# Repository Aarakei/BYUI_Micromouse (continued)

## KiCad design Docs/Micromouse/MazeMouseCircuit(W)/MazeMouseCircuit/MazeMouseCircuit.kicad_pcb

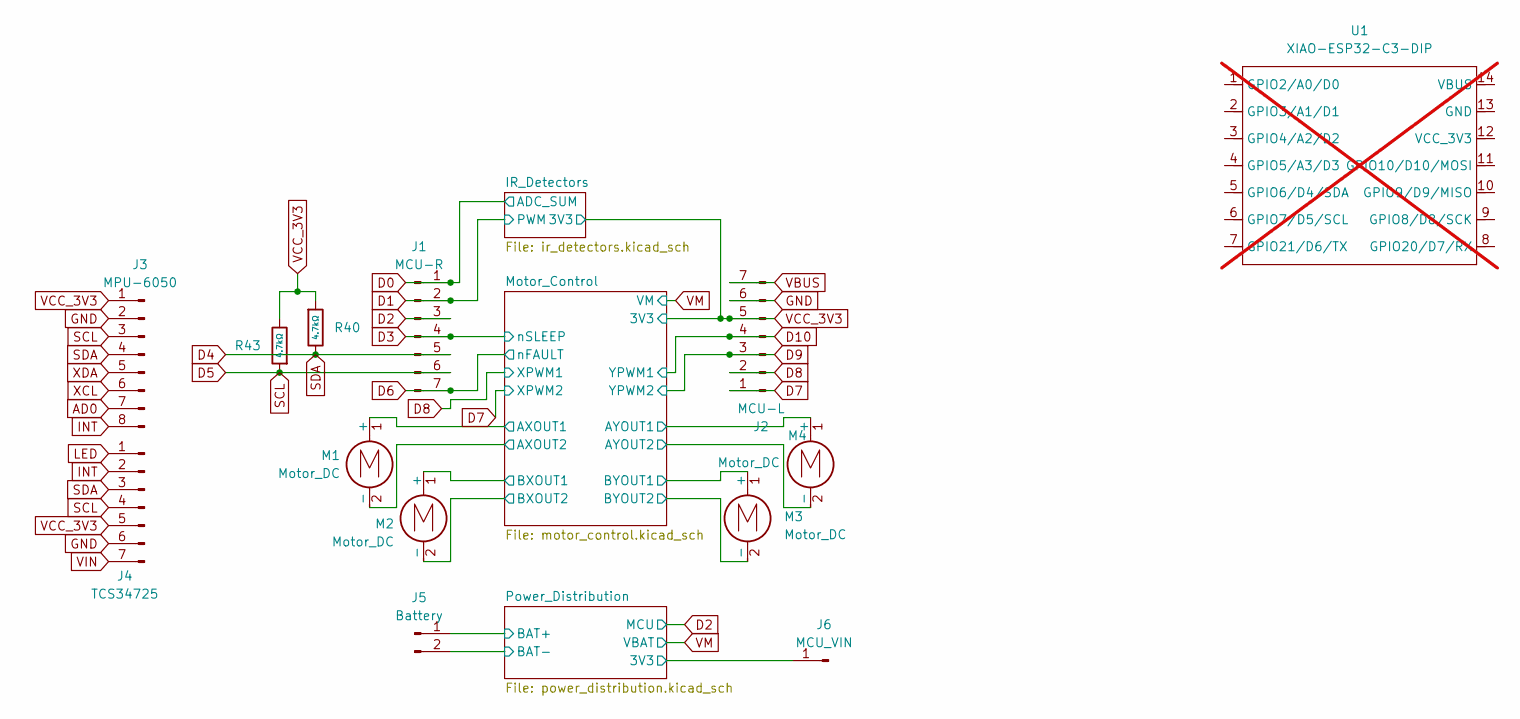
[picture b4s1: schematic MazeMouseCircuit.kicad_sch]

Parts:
J1: MCU-R; PinHeader_1x07_P2.54mm_Vertical
J2: MCU-L; PinHeader_1x07_P2.54mm_Vertical
J3: MPU-6050; PinHeader_1x08_P2.54mm_Vertical
J4: TCS34725; PinHeader_1x07_P2.54mm_Vertical
J5: Battery; PhoenixContact_GMSTBVA_2,5_2-G_1x02_P7.50mm_Vertical
J6: MCU_VIN; PinHeader_1x01_P2.00mm_Vertical
M1, M2, M3, M4: Motor_DC; PinHeader_2x01_P2.54mm_Vertical
R40, R43: 4.7kΩ; R_0402; Overload Voltage (Max) 50V; Tolerance ±1%; Part 0402WGF4701TCE; LCSC C25900
U1: XIAO-ESP32-C3-DIP; MOUDLE14P-XIAO-DIP-SMD; not fitted

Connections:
/Motor_Control/AXOUT1: M1.1 (+); also elsewhere on the board
/Motor_Control/AXOUT2: M1.2 (-); also elsewhere on the board
/Motor_Control/AYOUT1: M4.1 (+); also elsewhere on the board
/Motor_Control/AYOUT2: M4.2 (-); also elsewhere on the board
/Motor_Control/BXOUT1: M2.1 (+); also elsewhere on the board
/Motor_Control/BXOUT2: M2.2 (-); also elsewhere on the board
/Motor_Control/BYOUT1: M3.1 (+); also elsewhere on the board
/Motor_Control/BYOUT2: M3.2 (-); also elsewhere on the board
/Power_Distribution/3V3: J6.1; also elsewhere on the board
/Power_Distribution/BAT+: J5.1; also elsewhere on the board
AD0: J3.7
D0: J1.1; also elsewhere on the board
D1: J1.2; also elsewhere on the board
D2: J1.3; also elsewhere on the board
D3: J1.4; also elsewhere on the board
D4: J1.5, J3.4, J4.3, R40.2
D5: J1.6, J3.3, J4.4, R43.1
D6: J1.7; also elsewhere on the board
D7: J2.1; also elsewhere on the board
D8: J2.2; also elsewhere on the board
D9: J2.3; also elsewhere on the board
D10: J2.4; also elsewhere on the board
GND: J2.6, J3.2, J4.6, J5.2; also elsewhere on the board
INT: J3.8, J4.2
LED: J4.1
VBUS: J2.7
VCC_3V3: J2.5, J3.1, J4.5, R40.1, R43.2; also elsewhere on the board
VIN: J4.7
XCL: J3.6
XDA: J3.5

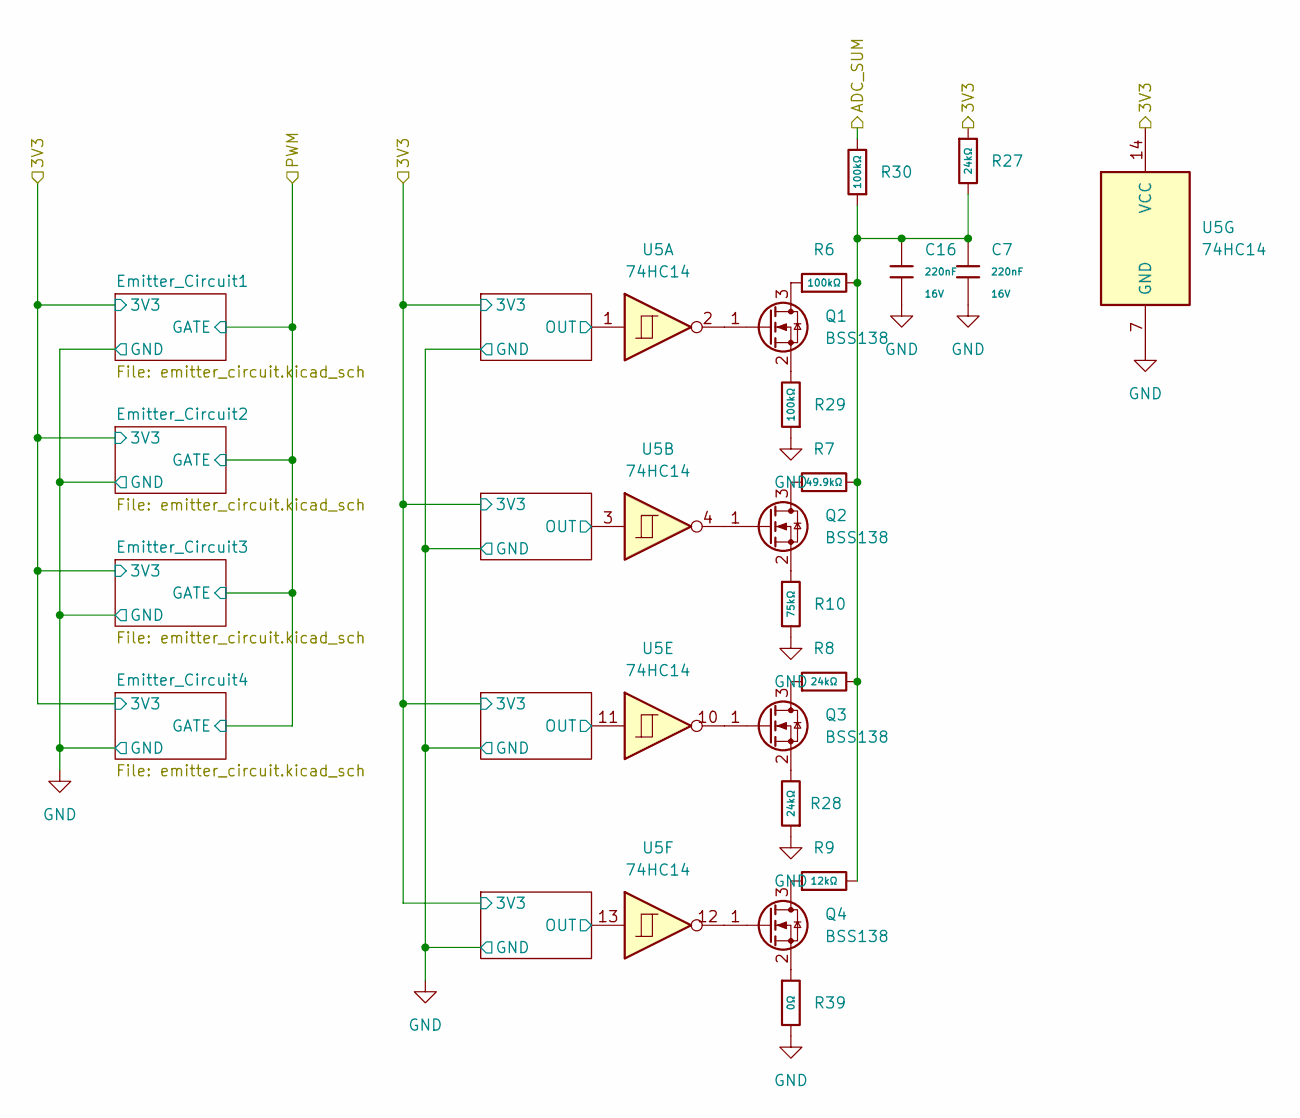
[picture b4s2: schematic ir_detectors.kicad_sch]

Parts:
C7, C16: 220nF; C_0402; Voltage Rated 16V; Tolerance ±10%; Part CL05B224KO5NNNC; LCSC C16772
Q1, Q2, Q3, Q4: BSS138; SOT-23
R6, R29, R30: 100kΩ; R_0603; Overload Voltage (Max) 75V; Tolerance ±1%; Part 0603WAF1003T5E; LCSC C25803
R7: 49.9kΩ; R_0402; Overload Voltage (Max) 50V; Tolerance ±1%; Part 0402WGF4992TCE; LCSC C25897
R8, R27, R28: 24kΩ; R_0402; Overload Voltage (Max) 50V; Tolerance ±1%; Part 0402WGF2402TCE; LCSC C25769
R9: 12kΩ; R_0402; Overload Voltage (Max) 50V; Tolerance ±1%; Part 0402WGF1202TCE; LCSC C25752
R10: 75kΩ; R_0402; Overload Voltage (Max) 50V; Tolerance ±1%; Part 0402WGF7502TCE; LCSC C25798
R39: 0Ω; R_0402; Overload Voltage (Max) 50V; Tolerance ±1%; Part 0402WGF0000TCE; LCSC C17168
U5: 74HC14; SOIC-14W_7.5x9mm_P1.27mm

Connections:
/IR_Detectors/Reveiver_Circuit1/OUT: U5.1; also elsewhere on the board
/IR_Detectors/Reveiver_Circuit2/OUT: U5.3; also elsewhere on the board
/IR_Detectors/Reveiver_Circuit3/OUT: U5.11; also elsewhere on the board
/IR_Detectors/Reveiver_Circuit4/OUT: U5.13; also elsewhere on the board
D0: R30.2; also elsewhere on the board
GND: C7.2, C16.2, R10.2, R28.1, R29.1, R39.2, U5.7 (GND); also elsewhere on the board
unnamed: C7.1, C16.1, R6.2, R7.2, R8.2, R9.2, R27.2, R30.1
unnamed: Q1.3 (D), R6.1
unnamed: Q1.1 (G), U5.2
unnamed: Q1.2 (S), R29.2
unnamed: Q2.3 (D), R7.1
unnamed: Q2.1 (G), U5.4
unnamed: Q2.2 (S), R10.1
unnamed: Q3.3 (D), R8.1
unnamed: Q3.1 (G), U5.10
unnamed: Q3.2 (S), R28.2
unnamed: Q4.3 (D), R9.1
unnamed: Q4.1 (G), U5.12
unnamed: Q4.2 (S), R39.1
VCC_3V3: R27.1, U5.14 (VCC); also elsewhere on the board

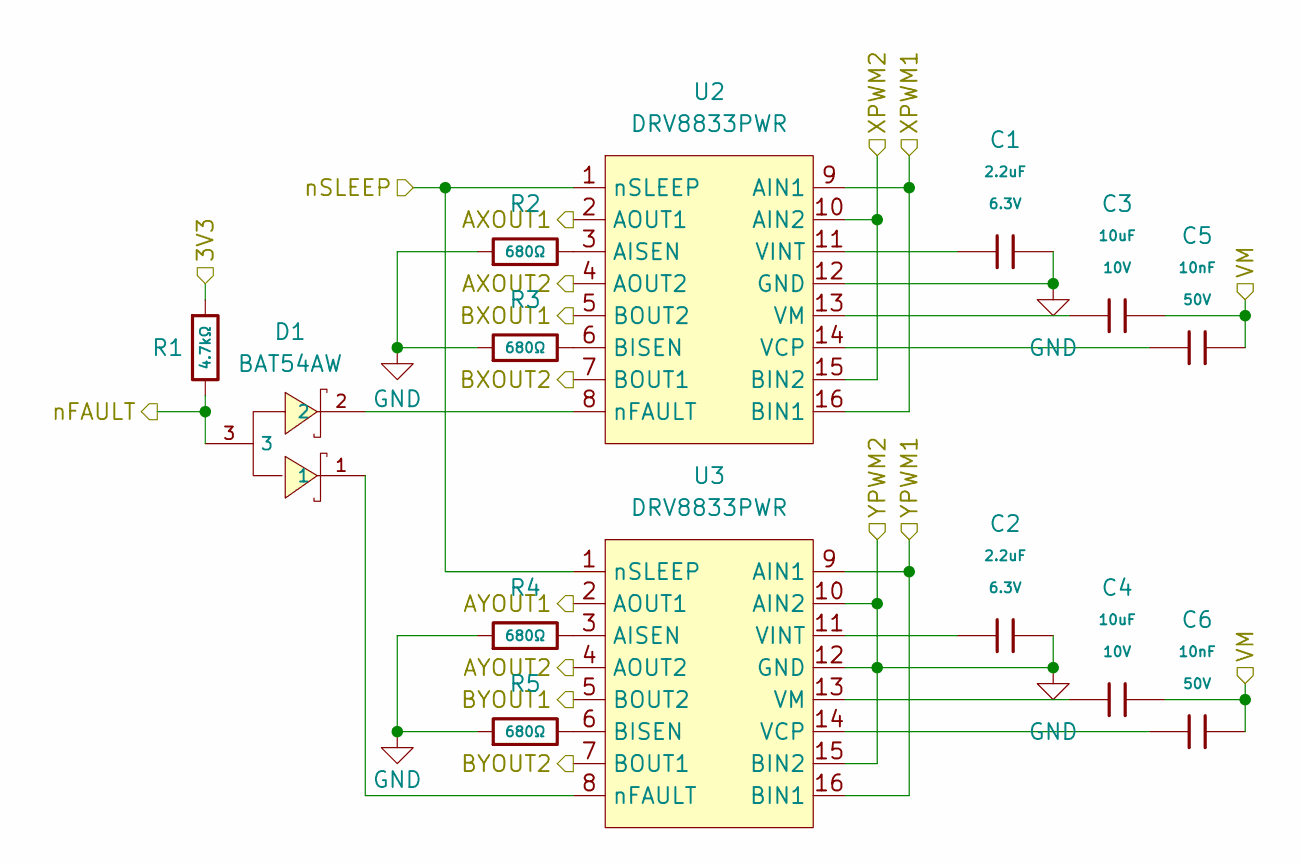
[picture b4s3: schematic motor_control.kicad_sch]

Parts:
C1, C2: 2.2uF; C_0402; Voltage Rated 6.3V; Tolerance ±20%; Part CL05A225MQ5NSNC; LCSC C12530
C3, C4: 10uF; C_0603; Voltage Rated 10V; Tolerance ±10%; Part CL10A106KP8NNNC; LCSC C19702
C5, C6: 10nF; C_0402; Voltage Rated 50V; Tolerance ±10%; Part CL05B103KB5NNNC; LCSC C15195
D1: BAT54AW; SOT-323-3_L2.0-W1.3-P1.30-LS2.3-BR; Part BAT54AW; LCSC C22466374
R1: 4.7kΩ; R_0402; Overload Voltage (Max) 50V; Tolerance ±1%; Part 0402WGF4701TCE; LCSC C25900
R2, R3, R4, R5: 680Ω; R_0402; Overload Voltage (Max) 50V; Tolerance ±1%; Part 0402WGF6800TCE; LCSC C25130
U2, U3: DRV8833PWR; TSSOP-16_4.4x5mm_P0.65mm

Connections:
/Motor_Control/AXOUT1: U2.2 (AOUT1); also elsewhere on the board
/Motor_Control/AXOUT2: U2.4 (AOUT2); also elsewhere on the board
/Motor_Control/AYOUT1: U3.2 (AOUT1); also elsewhere on the board
/Motor_Control/AYOUT2: U3.4 (AOUT2); also elsewhere on the board
/Motor_Control/BXOUT1: U2.5 (BOUT2); also elsewhere on the board
/Motor_Control/BXOUT2: U2.7 (BOUT1); also elsewhere on the board
/Motor_Control/BYOUT1: U3.5 (BOUT2); also elsewhere on the board
/Motor_Control/BYOUT2: U3.7 (BOUT1); also elsewhere on the board
D3: U2.1 (nSLEEP), U3.1 (nSLEEP); also elsewhere on the board
D6: D1.3, R1.2; also elsewhere on the board
D7: U2.10 (AIN2), U2.15 (BIN2); also elsewhere on the board
D8: U2.9 (AIN1), U2.16 (BIN1); also elsewhere on the board
D9: C1.2, C2.2, R2.1, R3.1, R4.1, R5.1, U2.12 (GND), U3.10 (AIN2), U3.12 (GND), U3.15 (BIN2); also elsewhere on the board
D10: U3.9 (AIN1), U3.16 (BIN1); also elsewhere on the board
unnamed: R2.2, U2.3 (AISEN)
unnamed: R3.2, U2.6 (BISEN)
unnamed: C5.2, U2.14 (VCP)
unnamed: C1.1, U2.11 (VINT)
unnamed: C3.1, U2.13 (VM)
unnamed: D1.2, U2.8 (nFAULT)
unnamed: R4.2, U3.3 (AISEN)
unnamed: R5.2, U3.6 (BISEN)
unnamed: C6.2, U3.14 (VCP)
unnamed: C2.1, U3.11 (VINT)
unnamed: C4.1, U3.13 (VM)
unnamed: D1.1, U3.8 (nFAULT)
VCC_3V3: R1.1; also elsewhere on the board
VM: C3.2, C4.2, C5.1, C6.1; also elsewhere on the board

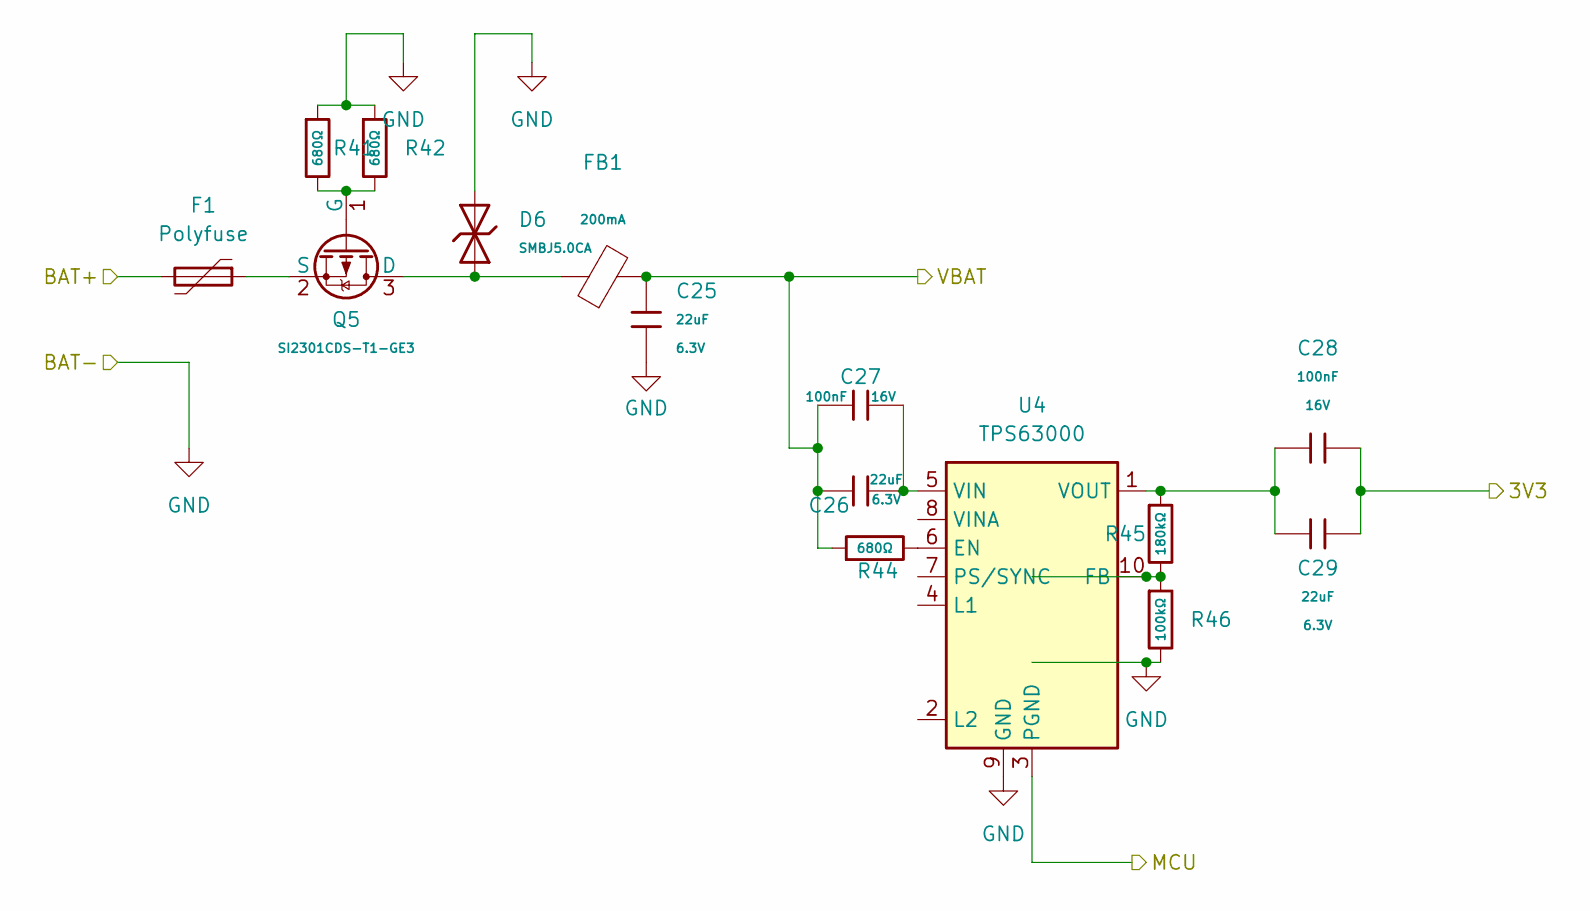
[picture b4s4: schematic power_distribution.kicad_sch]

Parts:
C25, C26, C29: 22uF; C_0603; Voltage Rated 6.3V; Tolerance ±20%; Part CL10A226MQ8NRNC; LCSC C59461
C27, C28: 100nF; C_0402; Voltage Rated 16V; Tolerance ±10%; Part CL05B104KO5NNNC; LCSC C1525
D6: SMBJ5.0CA; D_SMB; Part SMBJ5.0CA; LCSC C19077559
F1: Polyfuse; Fuse_0402_1005Metric
FB1: FB_0603; Current Rating 200mA; Tolerance ±25%; Part GZ1608D601TF; LCSC C1002
Q5: SI2301CDS-T1-GE3; Q_SOT-23; Part SI2301CDS-T1-GE3; LCSC C10487
R41, R42, R44: 680Ω; R_0402; Overload Voltage (Max) 50V; Tolerance ±1%; Part 0402WGF6800TCE; LCSC C25130
R45: 180kΩ; R_0603; Overload Voltage (Max) 75V; Tolerance ±1%; Part 0603WAF1803T5E; LCSC C22827
R46: 100kΩ; R_0603; Overload Voltage (Max) 75V; Tolerance ±1%; Part 0603WAF1003T5E; LCSC C25803
U4: TPS63000; Texas_DRC0010J_ThermalVias

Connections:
/Power_Distribution/3V3: C28.2, C29.1; also elsewhere on the board
/Power_Distribution/BAT+: F1.2; also elsewhere on the board
D2: U4.3 (PGND), U4.11 (PGND); also elsewhere on the board
GND: C25.2, D6.2, R41.1, R42.1, R46.2, U4.9 (GND); also elsewhere on the board
unnamed: D6.1, FB1.1, Q5.3 (D)
unnamed: Q5.1 (G), R41.2, R42.2
unnamed: F1.1, Q5.2 (S)
unnamed: R44.2, U4.6 (EN)
unnamed: R45.2, R46.1, U4.10 (FB)
unnamed: C26.1, C27.2, U4.5 (VIN)
unnamed: C28.1, C29.2, R45.1, U4.1 (VOUT)
VM: C25.1, C26.2, C27.1, FB1.2, R44.1; also elsewhere on the board

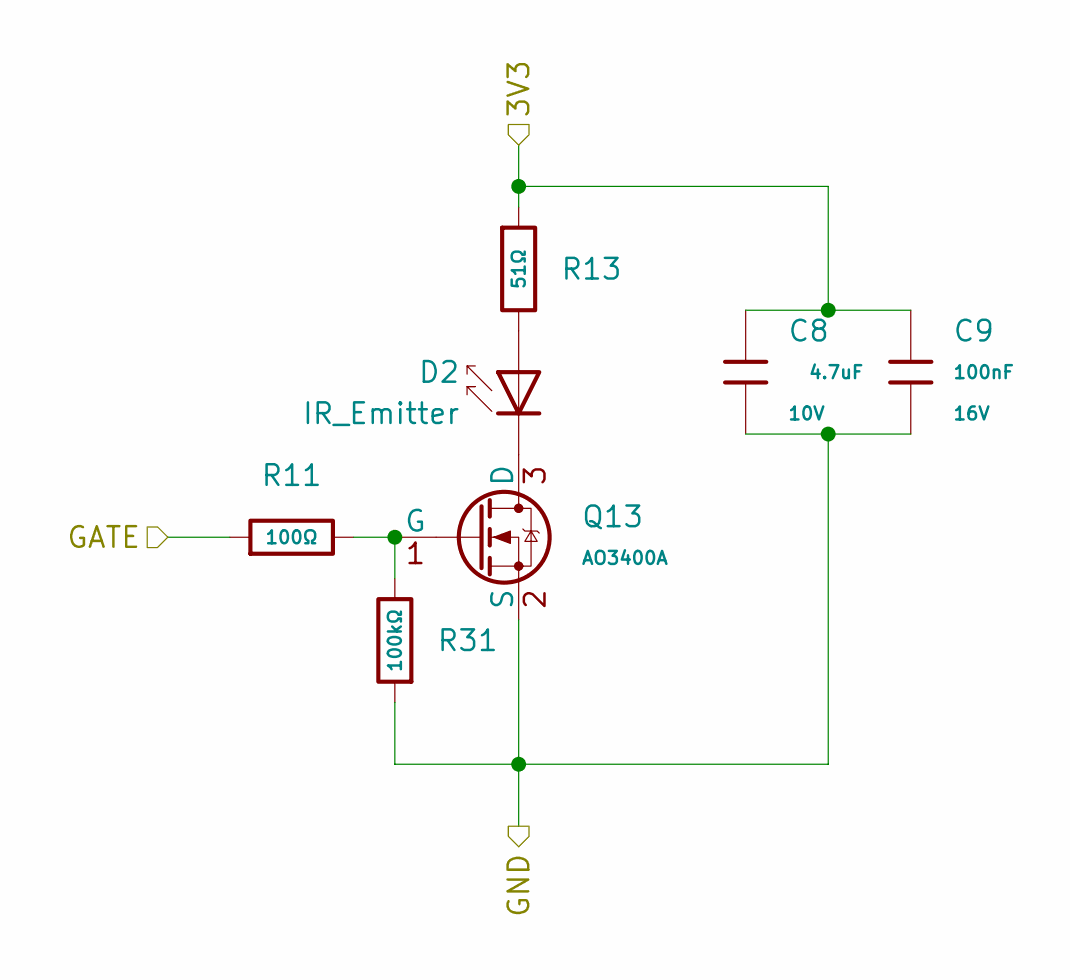
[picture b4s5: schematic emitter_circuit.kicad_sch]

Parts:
C8: 4.7uF; C_0402; Voltage Rated 10V; Tolerance ±20%; Part CL05A475MP5NRNC; LCSC C23733
C9: 100nF; C_0402; Voltage Rated 16V; Tolerance ±10%; Part CL05B104KO5NNNC; LCSC C1525
D2: IR_Emitter; LED_D5.0mm_Horizontal_O1.27mm_Z3.0mm_IRBlack
Q13: AO3400A; Q_SOT-23; Part AO3400A; LCSC C20917
R11: 100Ω; R_0402; Overload Voltage (Max) 50V; Tolerance ±1%; Part 0402WGF1000TCE; LCSC C25076
R13: 51Ω; R_0402; Overload Voltage (Max) 50V; Tolerance ±1%; Part 0402WGF510JTCE; LCSC C25125
R31: 100kΩ; R_0603; Overload Voltage (Max) 75V; Tolerance ±1%; Part 0603WAF1003T5E; LCSC C25803

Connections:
D1: R11.1; also elsewhere on the board
GND: C8.2, C9.2, Q13.2 (S), R31.1; also elsewhere on the board
unnamed: D2.2 (A), R13.2
unnamed: D2.1 (K), Q13.3 (D)
unnamed: Q13.1 (G), R11.2, R31.2
VCC_3V3: C8.1, C9.1, R13.1; also elsewhere on the board

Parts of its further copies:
C10, C12, C14: 4.7uF; C_0402; Voltage Rated 10V; Tolerance ±20%; Part CL05A475MP5NRNC; LCSC C23733
C11, C13, C15: 100nF; C_0402; Voltage Rated 16V; Tolerance ±10%; Part CL05B104KO5NNNC; LCSC C1525
D3, D4, D5: IR_Emitter; LED_D5.0mm_Horizontal_O1.27mm_Z3.0mm_IRBlack
Q14, Q15, Q16: AO3400A; Q_SOT-23; Part AO3400A; LCSC C20917
R15, R19, R23: 100Ω; R_0402; Overload Voltage (Max) 50V; Tolerance ±1%; Part 0402WGF1000TCE; LCSC C25076
R17, R21, R25: 51Ω; R_0402; Overload Voltage (Max) 50V; Tolerance ±1%; Part 0402WGF510JTCE; LCSC C25125
R32, R33, R34: 100kΩ; R_0603; Overload Voltage (Max) 75V; Tolerance ±1%; Part 0603WAF1003T5E; LCSC C25803

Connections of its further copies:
D1: R15.1, R19.1, R23.1; also elsewhere on the board
GND: C10.2, C11.2, C12.2, C13.2, C14.2, C15.2, Q14.2 (S), Q15.2 (S), Q16.2 (S), R32.1, R33.1, R34.1; also elsewhere on the board
unnamed: D3.2 (A), R17.2
unnamed: D3.1 (K), Q14.3 (D)
unnamed: D4.2 (A), R21.2
unnamed: D4.1 (K), Q15.3 (D)
unnamed: D5.2 (A), R25.2
unnamed: D5.1 (K), Q16.3 (D)
unnamed: Q14.1 (G), R15.2, R32.2
unnamed: Q15.1 (G), R19.2, R33.2
unnamed: Q16.1 (G), R23.2, R34.2
VCC_3V3: C10.1, C11.1, C12.1, C13.1, C14.1, C15.1, R17.1, R21.1, R25.1; also elsewhere on the board

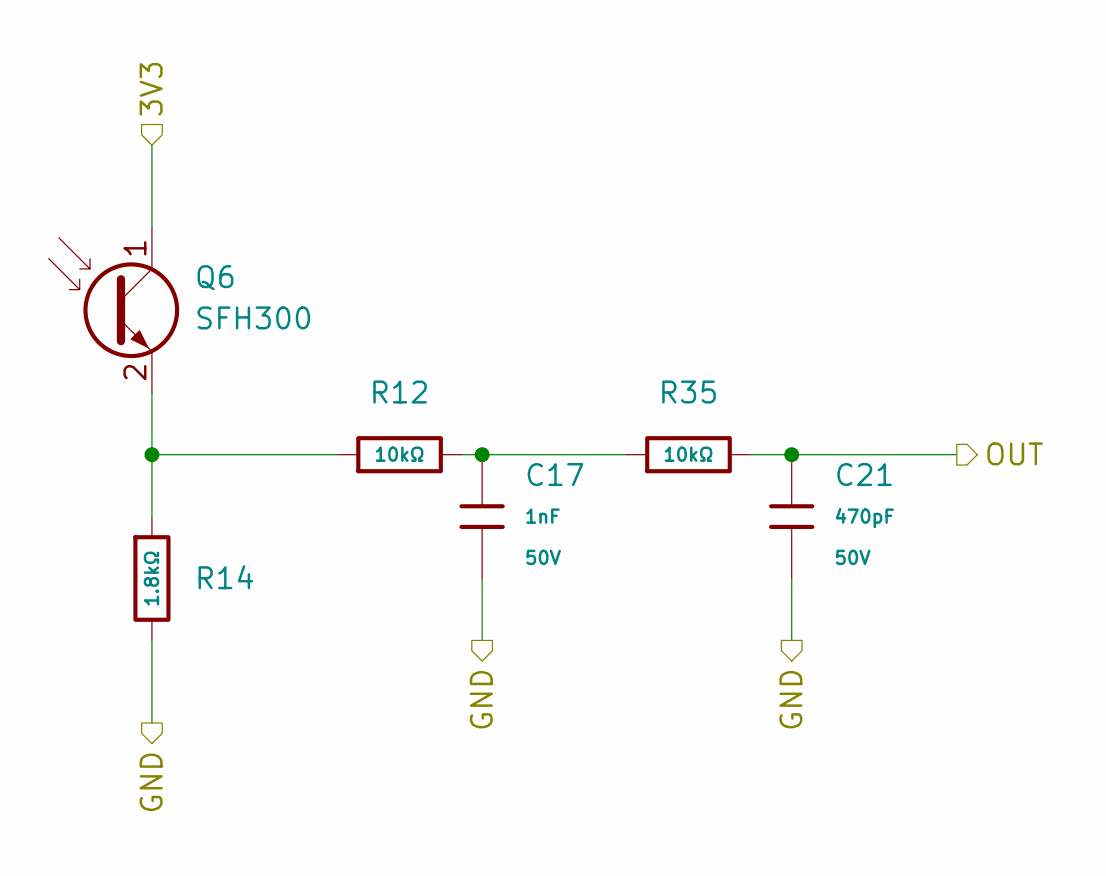
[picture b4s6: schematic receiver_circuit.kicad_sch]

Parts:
C17: 1nF; C_0402; Voltage Rated 50V; Tolerance ±10%; Part 0402B102K500NT; LCSC C1523
C21: 470pF; C_0402; Voltage Rated 50V; Tolerance ±10%; Part 0402B471K500NT; LCSC C1537
Q6: SFH300; LED_D5.0mm_Horizontal_O1.27mm_Z3.0mm_Clear
R12, R35: 10kΩ; R_0402; Overload Voltage (Max) 50V; Tolerance ±1%; Part 0402WGF1002TCE; LCSC C25744
R14: 1.8kΩ; R_0805; Overload Voltage (Max) 150V; Tolerance ±1%; Part 0805W8F1801T5E; LCSC C17398

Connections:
/IR_Detectors/Reveiver_Circuit1/OUT: C21.1, R35.2; also elsewhere on the board
GND: C17.2, C21.2, R14.2; also elsewhere on the board
unnamed: C17.1, R12.2, R35.1
unnamed: Q6.2 (E), R12.1, R14.1
VCC_3V3: Q6.1 (C); also elsewhere on the board

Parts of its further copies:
C18, C19, C20: 1nF; C_0402; Voltage Rated 50V; Tolerance ±10%; Part 0402B102K500NT; LCSC C1523
C22, C23, C24: 470pF; C_0402; Voltage Rated 50V; Tolerance ±10%; Part 0402B471K500NT; LCSC C1537
Q8, Q10, Q12: SFH300; LED_D5.0mm_Horizontal_O1.27mm_Z3.0mm_Clear
R16, R20, R24, R36, R37, R38: 10kΩ; R_0402; Overload Voltage (Max) 50V; Tolerance ±1%; Part 0402WGF1002TCE; LCSC C25744
R18, R22, R26: 1.8kΩ; R_0805; Overload Voltage (Max) 150V; Tolerance ±1%; Part 0805W8F1801T5E; LCSC C17398

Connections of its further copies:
/IR_Detectors/Reveiver_Circuit2/OUT: C22.1, R36.2; also elsewhere on the board
/IR_Detectors/Reveiver_Circuit3/OUT: C23.1, R37.2; also elsewhere on the board
/IR_Detectors/Reveiver_Circuit4/OUT: C24.1, R38.2; also elsewhere on the board
GND: C18.2, C19.2, C20.2, C22.2, C23.2, C24.2, R18.2, R22.2, R26.2; also elsewhere on the board
unnamed: C18.1, R16.2, R36.1
unnamed: C19.1, R20.2, R37.1
unnamed: C20.1, R24.2, R38.1
unnamed: Q8.2 (E), R16.1, R18.1
unnamed: Q10.2 (E), R20.1, R22.1
unnamed: Q12.2 (E), R24.1, R26.1
VCC_3V3: Q8.1 (C), Q10.1 (C), Q12.1 (C); also elsewhere on the board

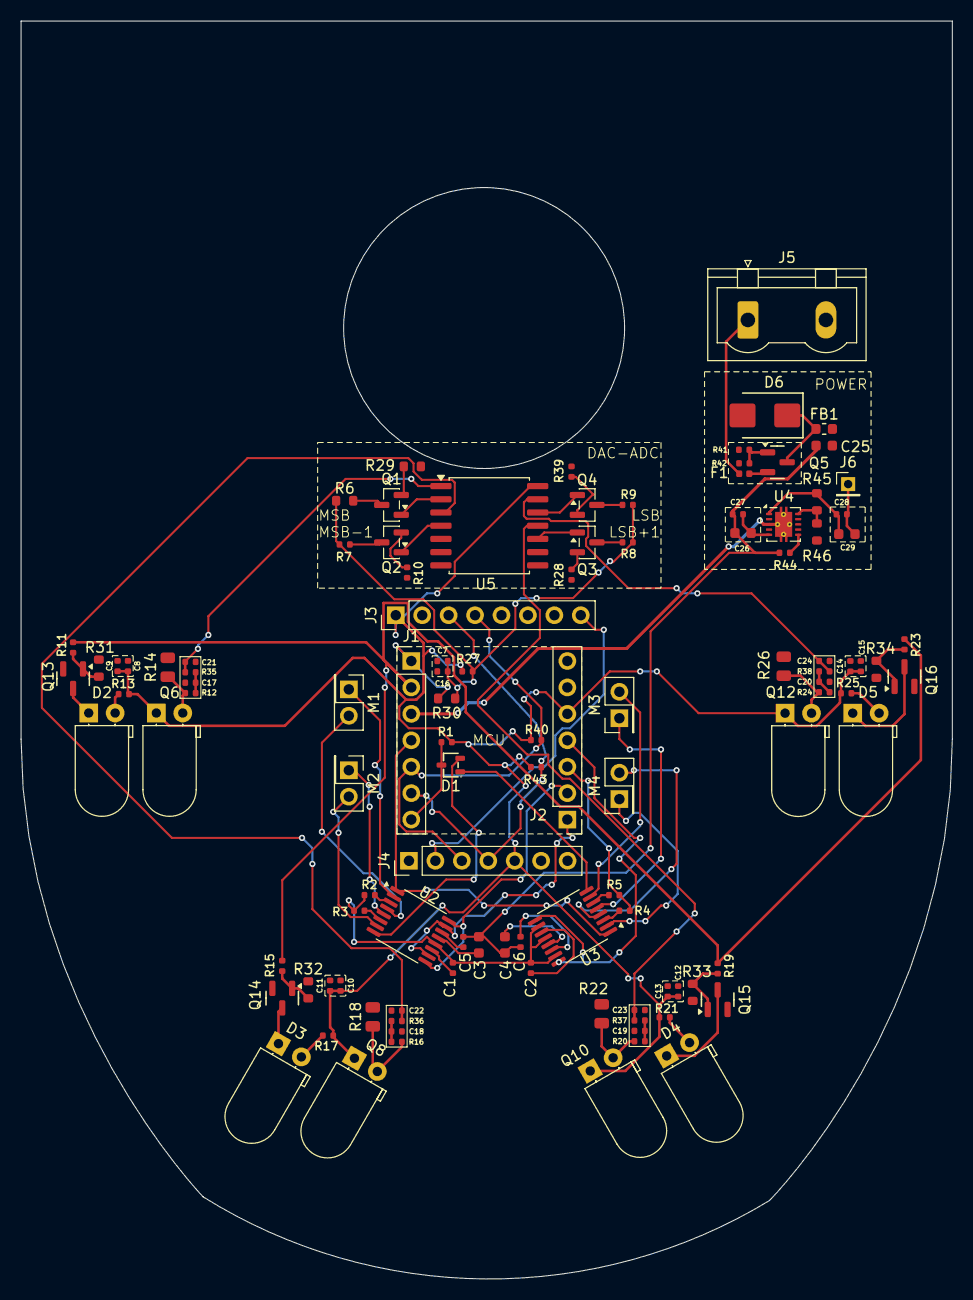
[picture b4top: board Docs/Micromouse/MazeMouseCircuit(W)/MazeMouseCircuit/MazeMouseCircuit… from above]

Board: 4 copper layers, 89.5 x 120.9 mm, 110 parts (0 on the bottom side), 81 nets.

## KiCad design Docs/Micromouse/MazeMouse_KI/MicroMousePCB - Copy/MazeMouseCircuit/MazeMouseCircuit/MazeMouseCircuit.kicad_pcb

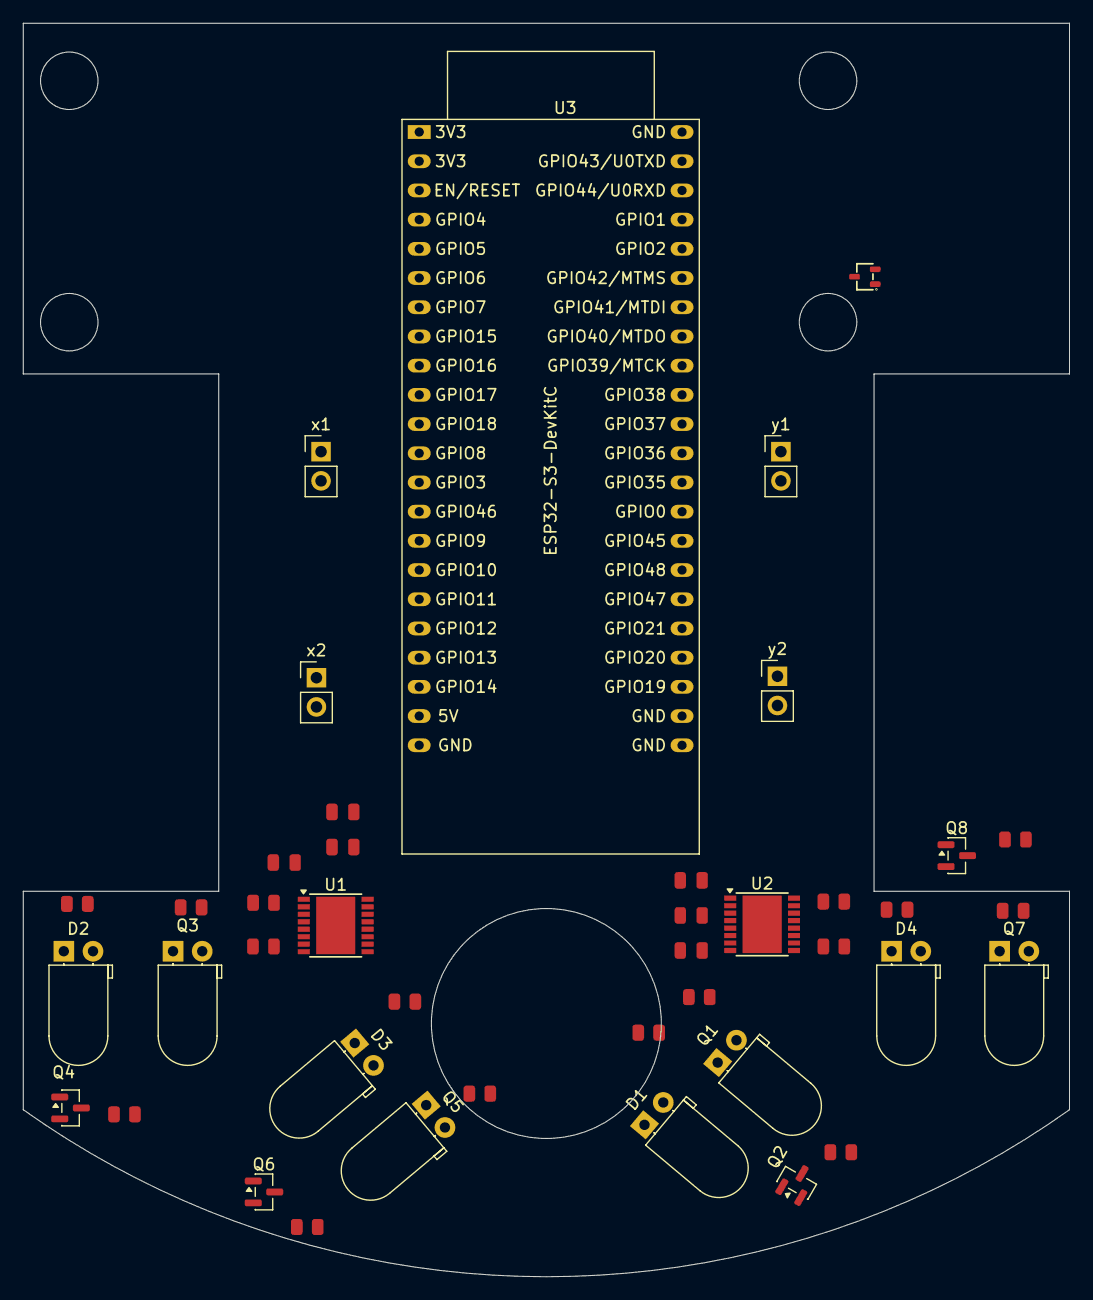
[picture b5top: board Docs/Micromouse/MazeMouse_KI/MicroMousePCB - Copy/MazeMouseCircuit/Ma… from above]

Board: 2 copper layers, 91.0 x 109.0 mm, 42 parts (0 on the bottom side), 46 nets, no tracks yet.

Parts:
C1, C5: 2.2uF; C_0805
C2, C6: 10uF; C_0805
C3, C4: 10nF; C_0805
D1, D2, D3, D4: IR204A; LED_D5.0mm_Horizontal_O1.27mm_Z3.0mm_IRBlack
D5: BAT54AW; SOT-323-3_L2.0-W1.3-P1.30-LS2.3-BR
Q1, Q3, Q5, Q7: SFH300; LED_D5.0mm_Horizontal_O1.27mm_Z3.0mm_Clear
Q2, Q4, Q6, Q8: AO3400A; SOT-23
R1, R3, R4, R6, R7, R9, R10, R12: 1kΩ; R_0805
R2, R5, R8, R11: 100Ω; R_0805
R13, R14, R15, R16: 0Ω; R_0805
U1, U2: DRV8833PWP; HTSSOP-16-1EP_4.4x5mm_P0.65mm_EP3.4x5mm
U3: ESP32-S3-DevKitC
x1, x2: Conn_01x02; PinHeader_1x02_P2.54mm_Vertical
y1, y2: Conn_01x02; PinHeader_1x02_P2.54mm_Vertical

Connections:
1in1: U1.9 (BIN1), U1.16 (AIN1), U3.11 (GPIO18/ADC2_CH7)
1in2: U1.10 (BIN2), U1.15 (AIN2), U3.12 (GPIO8/ADC1_CH7)
2in1: U2.9 (BIN1), U2.16 (AIN1), U3.9 (GPIO16/ADC2_CH5/32K_N)
2in2: U2.10 (BIN2), U2.15 (AIN2), U3.10 (GPIO17/ADC2_CH6)
+3V3: R1.1, R2.1, R4.1, R5.1, R7.1, R8.1, R10.1, R11.1
/Motor1/Aout1: U1.2 (AOUT1), x1.2
/Motor1/Aout2: U1.4 (AOUT2), x1.1
/Motor1/Bout1: U1.7 (BOUT1), x2.1
/Motor1/Bout2: U1.5 (BOUT2), x2.2
/Motor1/VM: C4.1, C6.1, U1.12 (VM)
/Motor/Aout1: U2.2 (AOUT1), y1.2
/Motor/Aout2: U2.4 (AOUT2), y1.1
/Motor/Bout1: U2.7 (BOUT1), y2.1
/Motor/Bout2: U2.5 (BOUT2), y2.2
/Motor/VM: C2.1, C3.1, U2.12 (VM)
GND: C1.1, C2.2, C5.1, C6.2, Q1.2 (E), Q2.2 (S), Q3.2 (E), Q4.2 (S), Q5.2 (E), Q6.2 (S), Q7.2 (E), Q8.2 (S), R3.2, R6.2, R9.2, R12.2, R13.1, R14.1, R15.1, R16.1, U1.13 (GND), U1.17 (GND), U2.13 (GND), U2.17 (GND)
unnamed: D1.2 (A), R2.2
unnamed: D1.1 (K), Q2.3 (D)
unnamed: D2.2 (A), R5.2
unnamed: D2.1 (K), Q4.3 (D)
unnamed: D3.2 (A), R8.2
unnamed: D3.1 (K), Q6.3 (D)
unnamed: D4.2 (A), R11.2
unnamed: D4.1 (K), Q8.3 (D)
unnamed: R15.2, U1.3 (AISEN)
unnamed: R16.2, U1.6 (BISEN)
unnamed: C4.2, U1.11 (VCP)
unnamed: C5.2, U1.14 (VINT)
unnamed: R13.2, U2.3 (AISEN)
unnamed: R14.2, U2.6 (BISEN)
unnamed: C3.2, U2.11 (VCP)
unnamed: C1.2, U2.14 (VINT)
unnamed: U3.1 (3V3), U3.2 (3V3)
unnamed: U3.22 (GND), U3.23 (GND), U3.24 (GND), U3.44 (GND)
RxA: Q1.1 (C), R1.2, U3.5 (GPIO5/ADC1_CH4)
RxB: Q3.1 (C), R4.2, U3.7 (GPIO7/ADC1_CH6)
RxC: Q7.1 (C), R10.2, U3.16 (GPIO10/ADC1_CH9)
RxD: Q5.1 (C), R7.2, U3.19 (GPIO13/ADC2_CH2)
TxA: Q2.1 (G), R3.1, U3.4 (GPIO4/ADC1_CH3)
TxB: Q4.1 (G), R6.1, U3.6 (GPIO6/ADC1_CH5)
TxC: Q8.1 (G), R12.1, U3.15 (GPIO9/ADC1_CH8)
TxD: Q6.1 (G), R9.1, U3.17 (GPIO11/ADC2_CH0)
nFault: D5.3, U3.14 (GPIO46)
nFaultx: D5.2, U1.8 (~FAULT)
nFaulty: D5.1, U2.8 (~FAULT)
nSleep: U1.1 (~SLEEP), U2.1 (~SLEEP), U3.13 (GPIO3/ADC1_CH2)

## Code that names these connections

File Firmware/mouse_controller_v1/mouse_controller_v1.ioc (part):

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Mcu.Name=STM32H743VITx
Mcu.Package=LQFP100
Mcu.UserName=STM32H743VITx
PA0.GPIOParameters=GPIO_Label
PA0.GPIO_Label=IR1Read
PA0.Mode=IN16-Single-Ended
PA0.Signal=ADC1_INP16
PA1.GPIOParameters=GPIO_Label
PA1.GPIO_Label=IR1Toggle
PA1.Signal=GPIO_Output
PA11.Mode=Device_Only
PA11.Signal=USB_OTG_FS_DM
PA12.Mode=Device_Only
PA12.Signal=USB_OTG_FS_DP
PA13\ (JTMS/SWDIO).Mode=Serial_Wire
PA13\ (JTMS/SWDIO).Signal=DEBUG_JTMS-SWDIO
PA14\ (JTCK/SWCLK).Mode=Serial_Wire
PA14\ (JTCK/SWCLK).Signal=DEBUG_JTCK-SWCLK
PA15\ (JTDI).GPIOParameters=GPIO_Label
PA15\ (JTDI).GPIO_Label=Motor1In2
PA15\ (JTDI).Signal=S_TIM2_CH1_ETR
PA4.GPIOParameters=GPIO_Label
PA4.GPIO_Label=MotorNSleep
PA4.Signal=GPIO_Output
PB0.GPIOParameters=GPIO_Label
PB0.GPIO_Label=IR2Read
PB0.Signal=ADCx_INP9
PB1.GPIOParameters=GPIO_Label
PB1.GPIO_Label=IR2Toggle
PB1.Signal=GPIO_Output
PB11.GPIOParameters=GPIO_Label
PB11.GPIO_Label=Motor1In1
PB11.Signal=S_TIM2_CH4
PC1.GPIOParameters=GPIO_PuPd,GPIO_Label
PC1.GPIO_Label=MotorNFault
PC1.GPIO_PuPd=GPIO_PULLUP
PC1.Signal=GPIO_Input
PC8.GPIOParameters=GPIO_Label
PC8.GPIO_Label=IR4Read
PC8.Signal=GPIO_Input
PC9.GPIOParameters=GPIO_Label
PC9.GPIO_Label=IR4Toggle
PC9.Signal=GPIO_Output
PD12.GPIOParameters=GPIO_Label
PD12.GPIO_Label=IR3Read
PD12.Signal=GPIO_Input
PD13.GPIOParameters=GPIO_Label
PD13.GPIO_Label=IR3Toggle
PD13.Signal=GPIO_Output
PD3.GPIOParameters=GPIO_Label
PD3.GPIO_Label=Q9
PD3.Signal=GPIO_Input
PD4.GPIOParameters=GPIO_Label
PD4.GPIO_Label=D6
PD4.Signal=GPIO_Output
PE13.GPIOParameters=GPIO_Label
PE13.GPIO_Label=Motor2In2
PE13.Signal=S_TIM1_CH3
PE14.GPIOParameters=GPIO_Label
PE14.GPIO_Label=Motor2In1
PE14.Signal=S_TIM1_CH4
PE2.GPIOParameters=GPIO_Label
PE2.GPIO_Label=D2
PE2.Signal=GPIO_Output
RCC.SYSCLKFreq_VALUE=64000000
board=custom
